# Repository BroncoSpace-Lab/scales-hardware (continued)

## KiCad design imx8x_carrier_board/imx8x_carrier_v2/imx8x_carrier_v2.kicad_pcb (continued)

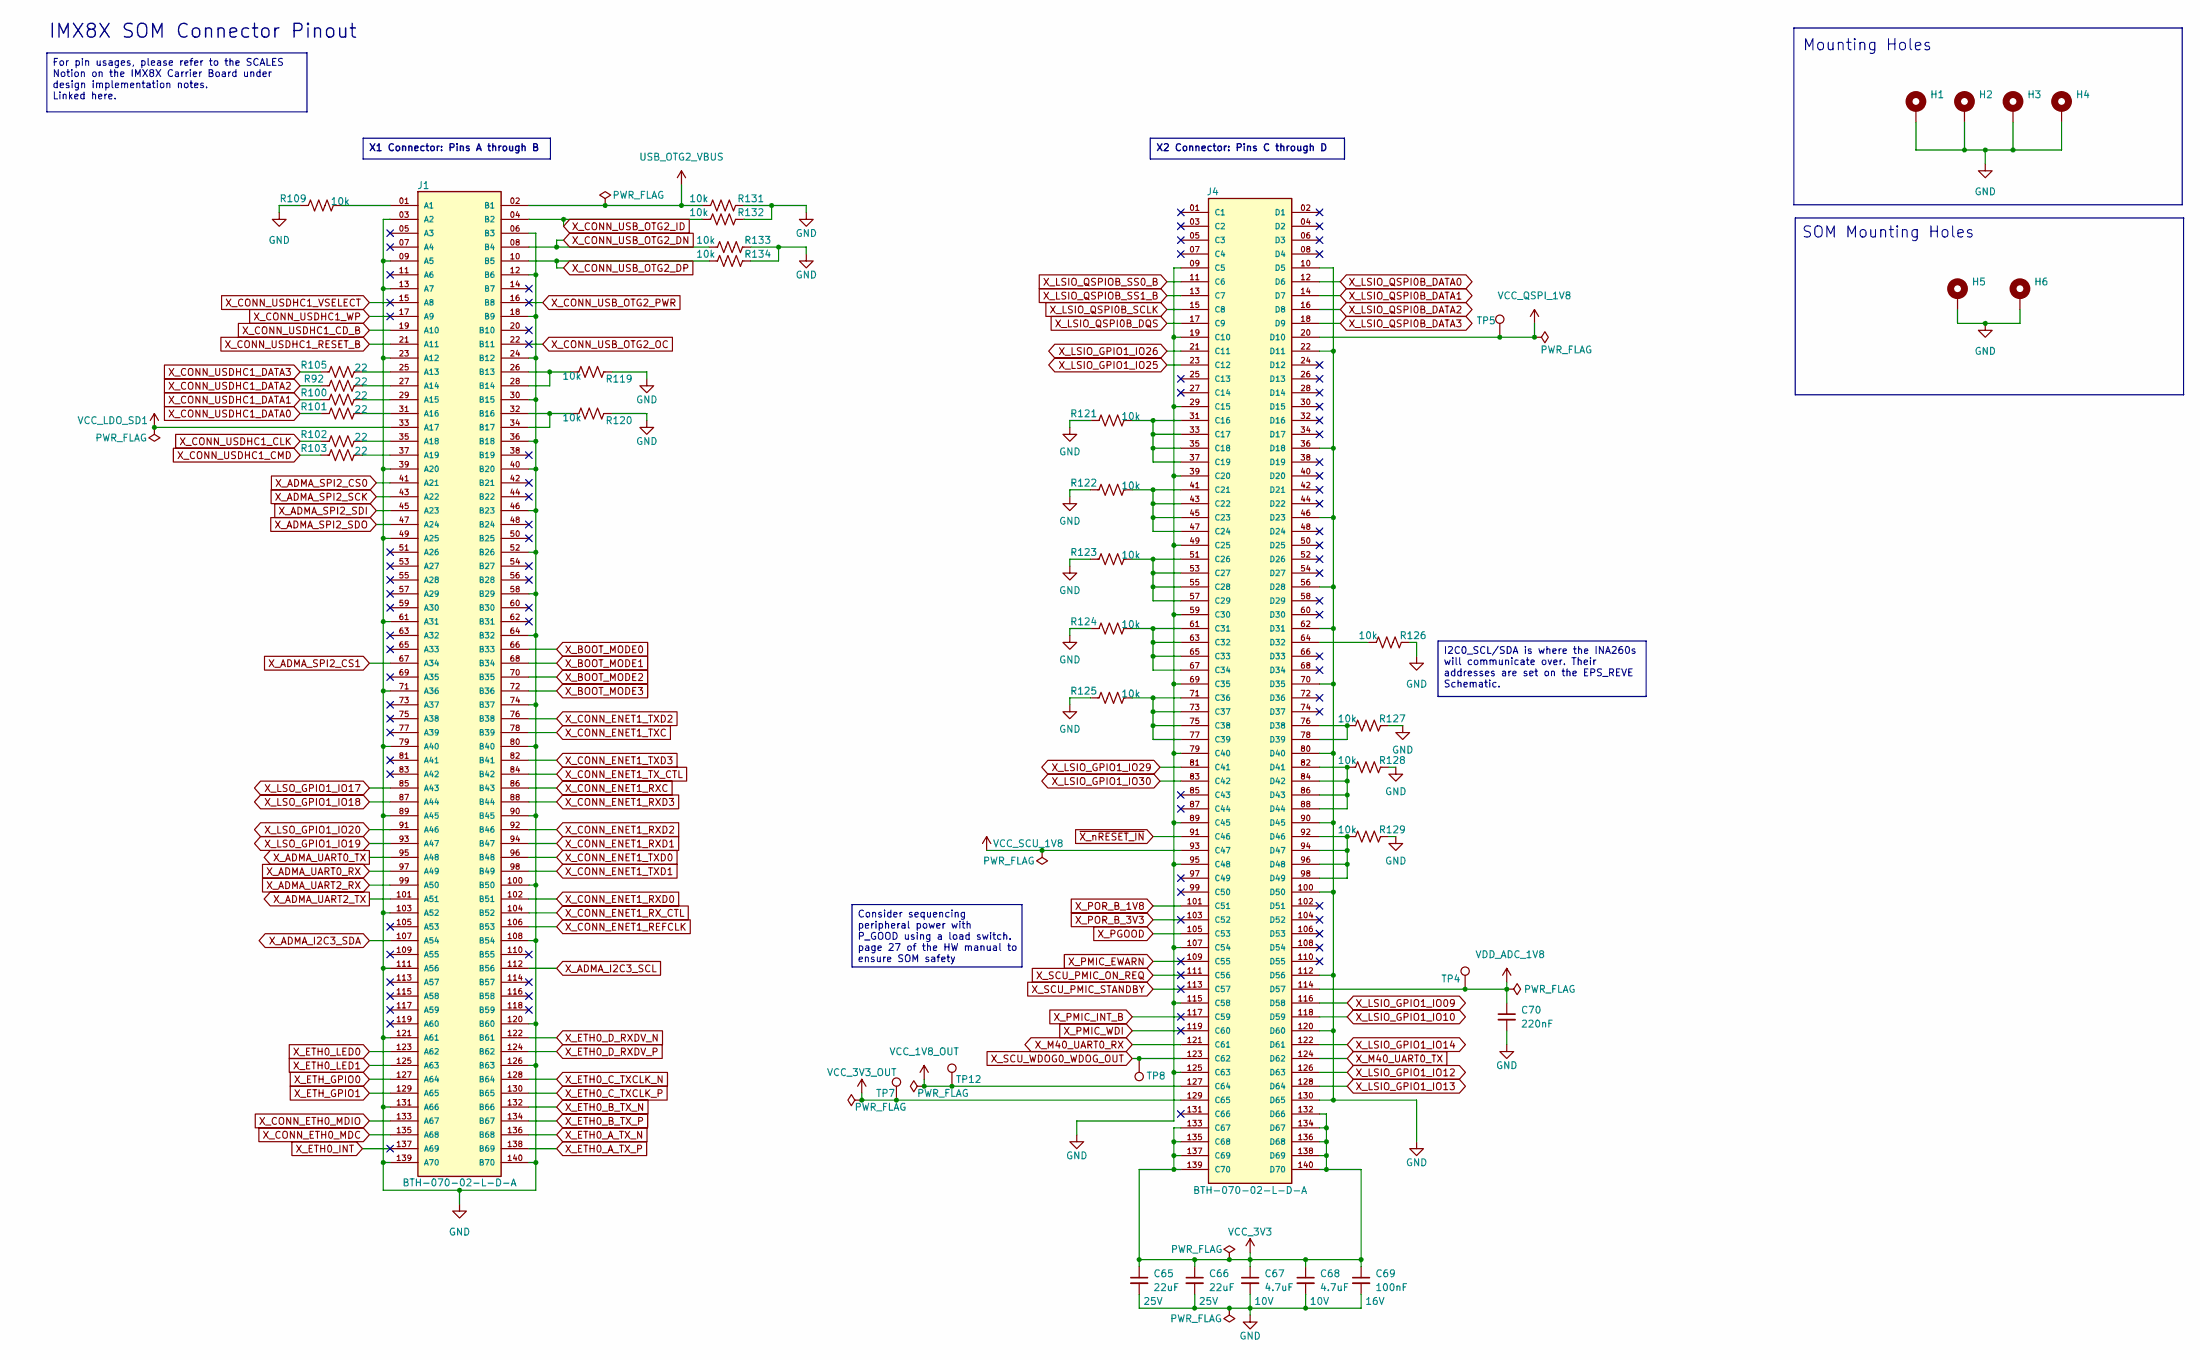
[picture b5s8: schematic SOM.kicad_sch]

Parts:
C65, C66: 22uF; C_0603_1608Metric; Voltage 25V
C67, C68: 4.7uF; C_0603_1608Metric; Voltage 10V
C69: 100nF; C_0603_1608Metric; Voltage 16V
C70: 220nF; C_0603_1608Metric
H1, H2, H3, H4: M3; MountingHole_2.7mm_M2.5_DIN965_Pad
H5, H6: MountingHole_Pad_M2.5_2.7mm; MountingHole_2.7mm_M2.5_DIN965_Pad
J1, J4: BTH-070-02-L-D-A; SAMTEC_BTH-070-02-L-D-A; PARTREV R
R92, R100, R101, R102, R103, R105: 22; R_0402_1005Metric
R109, R119, R120, R121, R122, R123, R124, R125, R126, R127, R128, R129, R131, R132, R133, R134: 10k; R_0402_1005Metric
TP4, TP5, TP7, TP8, TP12: TestPoint; TestPoint_THTPad_1.0x1.0mm_Drill0.5mm

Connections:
GND: C65.2, C66.2, C67.2, C68.2, C69.2, C70.2, H1.1 (MP), H2.1 (MP), H3.1 (MP), H4.1 (MP), H5.1 (MP), H6.1 (MP), J1.03 (A2), J1.06 (B3), J1.09 (A5), J1.12 (B6), J1.13 (A7), J1.18 (B9), J1.23 (A12), J1.24 (B12), J1.30 (B15), J1.36 (B18), J1.39 (A20), J1.40 (B20), J1.46 (B23), J1.49 (A25), J1.52 (B26), J1.58 (B29), J1.61 (A31), J1.64 (B32), J1.71 (A36), J1.74 (B37), J1.79 (A40), J1.80 (B40), J1.89 (A45), J1.90 (B45), J1.100 (B50), J1.103 (A52), J1.108 (B54), J1.111 (A56), J1.120 (B60), J1.121 (A61), J1.126 (B63), J1.131 (A66), J1.139 (A70), J1.140 (B70), J4.09 (C5), J4.10 (D5), J4.19 (C10), J4.22 (D11), J4.29 (C15), J4.36 (D18), J4.39 (C20), J4.46 (D23), J4.49 (C25), J4.56 (D28), J4.59 (C30), J4.62 (D31), J4.69 (C35), J4.70 (D35), J4.79 (C40), J4.80 (D40), J4.89 (C45), J4.90 (D45), J4.95 (C48), J4.100 (D50), J4.107 (C54), J4.112 (D56), J4.115 (C58), J4.120 (D60), J4.125 (C63), J4.130 (D65), R109.1, R119.1, R120.1, R121.1, R122.1, R123.1, R124.1, R125.1, R126.1, R127.1, R128.1, R129.1, R131.1, R132.1, R133.1, R134.1; also elsewhere on the board
unnamed: J1.01 (A1), R109.2
unnamed: J1.25 (A13), R105.2
unnamed: J1.27 (A14), R92.2
unnamed: J1.29 (A15), R100.2
unnamed: J1.31 (A16), R101.2
unnamed: J1.35 (A18), R102.2
unnamed: J1.37 (A19), R103.2
unnamed: J1.26 (B13), J1.28 (B14), R119.2
unnamed: J1.32 (B16), J1.34 (B17), R120.2
unnamed: J4.31 (C16), J4.33 (C17), J4.35 (C18), J4.37 (C19), R121.2
unnamed: J4.41 (C21), J4.43 (C22), J4.45 (C23), J4.47 (C24), R122.2
unnamed: J4.51 (C26), J4.53 (C27), J4.55 (C28), J4.57 (C29), R123.2
unnamed: J4.61 (C31), J4.63 (C32), J4.65 (C33), J4.67 (C34), R124.2
unnamed: J4.71 (C36), J4.73 (C37), J4.75 (C38), J4.77 (C39), R125.2
unnamed: J4.64 (D32), R126.2
unnamed: J4.76 (D38), J4.78 (D39), R127.2
unnamed: J4.82 (D41), J4.84 (D42), J4.86 (D43), J4.88 (D44), R128.2
unnamed: J4.92 (D46), J4.94 (D47), J4.96 (D48), J4.98 (D49), R129.2
USB_OTG2_VBUS: J1.02 (B1), R131.2
VCC_1V8_OUT: J4.127 (C64), TP12.1; also elsewhere on the board
VCC_3V3: C65.1, C66.1, C67.1, C68.1, C69.1, J4.132 (D66), J4.133 (C67), J4.134 (D67), J4.135 (C68), J4.136 (D68), J4.137 (C69), J4.138 (D69), J4.139 (C70), J4.140 (D70); also elsewhere on the board
VCC_3V3_OUT: J4.129 (C65), TP7.1; also elsewhere on the board
VCC_LDO_SD1: J1.33 (A17); also elsewhere on the board
VCC_QSPI_1V8: J4.20 (D10), TP5.1
VCC_SCU_1V8: J4.93 (C47); also elsewhere on the board
VDD_ADC_1V8: C70.1, J4.114 (D57), TP4.1
X_ADMA_I2C3_SCL: J1.112 (B56); also elsewhere on the board
X_ADMA_I2C3_SDA: J1.107 (A54); also elsewhere on the board
X_ADMA_SPI2_CS0: J1.41 (A21); also elsewhere on the board
X_ADMA_SPI2_CS1: J1.67 (A34); also elsewhere on the board
X_ADMA_SPI2_SCK: J1.43 (A22); also elsewhere on the board
X_ADMA_SPI2_SDI: J1.45 (A23); also elsewhere on the board
X_ADMA_SPI2_SDO: J1.47 (A24); also elsewhere on the board
X_ADMA_UART0_RX: J1.97 (A49); also elsewhere on the board
X_ADMA_UART0_TX: J1.95 (A48); also elsewhere on the board
X_ADMA_UART2_RX: J1.99 (A50); also elsewhere on the board
X_ADMA_UART2_TX: J1.101 (A51); also elsewhere on the board
X_BOOT_MODE0: J1.66 (B33); also elsewhere on the board
X_BOOT_MODE1: J1.68 (B34); also elsewhere on the board
X_BOOT_MODE2: J1.70 (B35); also elsewhere on the board
X_BOOT_MODE3: J1.72 (B36); also elsewhere on the board
X_CONN_ENET1_REFCLK: J1.106 (B53); also elsewhere on the board
X_CONN_ENET1_RXC: J1.86 (B43); also elsewhere on the board
X_CONN_ENET1_RXD0: J1.102 (B51); also elsewhere on the board
X_CONN_ENET1_RXD1: J1.94 (B47); also elsewhere on the board
X_CONN_ENET1_RXD2: J1.92 (B46); also elsewhere on the board
X_CONN_ENET1_RXD3: J1.88 (B44); also elsewhere on the board
X_CONN_ENET1_RX_CTL: J1.104 (B52); also elsewhere on the board
X_CONN_ENET1_TXC: J1.78 (B39); also elsewhere on the board
X_CONN_ENET1_TXD0: J1.96 (B48); also elsewhere on the board
X_CONN_ENET1_TXD1: J1.98 (B49); also elsewhere on the board
X_CONN_ENET1_TXD2: J1.76 (B38); also elsewhere on the board
X_CONN_ENET1_TXD3: J1.82 (B41); also elsewhere on the board
X_CONN_ENET1_TX_CTL: J1.84 (B42); also elsewhere on the board
X_CONN_ETH0_MDC: J1.135 (A68); also elsewhere on the board
X_CONN_ETH0_MDIO: J1.133 (A67); also elsewhere on the board
X_CONN_USB_OTG2_DN: J1.08 (B4), R133.2
X_CONN_USB_OTG2_DP: J1.10 (B5), R134.2
X_CONN_USB_OTG2_ID: J1.04 (B2), R132.2
X_CONN_USB_OTG2_OC: J1.22 (B11)
X_CONN_USB_OTG2_PWR: J1.16 (B8)
X_CONN_USDHC1_CD_B: J1.19 (A10); also elsewhere on the board
X_CONN_USDHC1_CLK: R102.1; also elsewhere on the board
X_CONN_USDHC1_CMD: R103.1; also elsewhere on the board
X_CONN_USDHC1_DATA0: R101.1; also elsewhere on the board
X_CONN_USDHC1_DATA1: R100.1; also elsewhere on the board
X_CONN_USDHC1_DATA2: R92.1; also elsewhere on the board
X_CONN_USDHC1_DATA3: R105.1; also elsewhere on the board
X_CONN_USDHC1_RESET_B: J1.21 (A11); also elsewhere on the board
X_CONN_USDHC1_VSELECT: J1.15 (A8)
X_CONN_USDHC1_WP: J1.17 (A9)
X_ETH0_A_TX_N: J1.136 (B68); also elsewhere on the board
X_ETH0_A_TX_P: J1.138 (B69); also elsewhere on the board
X_ETH0_B_TX_N: J1.132 (B66); also elsewhere on the board
X_ETH0_B_TX_P: J1.134 (B67); also elsewhere on the board
X_ETH0_C_TXCLK_N: J1.128 (B64); also elsewhere on the board
X_ETH0_C_TXCLK_P: J1.130 (B65); also elsewhere on the board
X_ETH0_D_RXDV_N: J1.122 (B61); also elsewhere on the board
X_ETH0_D_RXDV_P: J1.124 (B62); also elsewhere on the board
X_ETH0_INT: J1.137 (A69)
X_ETH0_LED0: J1.123 (A62); also elsewhere on the board
X_ETH0_LED1: J1.125 (A63); also elsewhere on the board
X_ETH_GPIO0: J1.127 (A64); also elsewhere on the board
X_ETH_GPIO1: J1.129 (A65); also elsewhere on the board
X_LSIO_GPIO1_IO09: J4.116 (D58); also elsewhere on the board
X_LSIO_GPIO1_IO10: J4.118 (D59); also elsewhere on the board
X_LSIO_GPIO1_IO12: J4.126 (D63); also elsewhere on the board
X_LSIO_GPIO1_IO13: J4.128 (D64); also elsewhere on the board
X_LSIO_GPIO1_IO14: J4.122 (D61); also elsewhere on the board
X_LSIO_GPIO1_IO25: J4.23 (C12); also elsewhere on the board
X_LSIO_GPIO1_IO26: J4.21 (C11); also elsewhere on the board
X_LSIO_GPIO1_IO29: J4.81 (C41); also elsewhere on the board
X_LSIO_GPIO1_IO30: J4.83 (C42); also elsewhere on the board
X_LSIO_QSPI0B_DATA0: J4.12 (D6); also elsewhere on the board
X_LSIO_QSPI0B_DATA1: J4.14 (D7); also elsewhere on the board
X_LSIO_QSPI0B_DATA2: J4.16 (D8); also elsewhere on the board
X_LSIO_QSPI0B_DATA3: J4.18 (D9); also elsewhere on the board
X_LSIO_QSPI0B_DQS: J4.17 (C9); also elsewhere on the board
X_LSIO_QSPI0B_SCLK: J4.15 (C8); also elsewhere on the board
X_LSIO_QSPIOB_SS0_B: J4.11 (C6); also elsewhere on the board
X_LSIO_QSPIOB_SS1_B: J4.13 (C7); also elsewhere on the board
X_LSO_GPIO1_IO17: J1.85 (A43); also elsewhere on the board
X_LSO_GPIO1_IO18: J1.87 (A44); also elsewhere on the board
X_LSO_GPIO1_IO19: J1.93 (A47); also elsewhere on the board
X_LSO_GPIO1_IO20: J1.91 (A46); also elsewhere on the board
X_M40_UART0_RX: J4.121 (C61); also elsewhere on the board
X_M40_UART0_TX: J4.124 (D62); also elsewhere on the board
X_PGOOD: J4.105 (C53); also elsewhere on the board
X_PMIC_EWARN: J4.109 (C55)
X_PMIC_INT_B: J4.117 (C59)
X_PMIC_WDI: J4.119 (C60)
X_POR_B_1V8: J4.101 (C51); also elsewhere on the board
X_POR_B_3V3: J4.103 (C52)
X_SCU_PMIC_ON_REQ: J4.111 (C56)
X_SCU_PMIC_STANDBY: J4.113 (C57)
X_SCU_WDOG0_WDOG_OUT: J4.123 (C62), TP8.1; also elsewhere on the board
~X_nRESET_IN: J4.91 (C46); also elsewhere on the board

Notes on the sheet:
Mounting Holes
SOM Mounting Holes
IMX8X SOM Connector Pinout
Consider sequencing peripheral power with P_GOOD using a load switch. page 27 of the HW manual to ensure SOM safety
X2 Connector: Pins C through D
I2C0_SCL/SDA is where the INA260s will communicate over. Their addresses are set on the EPS_REVE Schematic.
For pin usages, please refer to the SCALES Notion on the IMX8X Carrier Board under design implementation notes. Linked here.
X1 Connector: Pins A through B

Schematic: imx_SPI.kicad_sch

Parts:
J6: Conn_02x07_Counter_Clockwise; PinHeader_2x07_P2.54mm_Vertical

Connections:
GND: J6.8; also elsewhere on the board
X_ADMA_SPI2_CS0: J6.1; also elsewhere on the board
X_ADMA_SPI2_CS1: J6.2; also elsewhere on the board
X_ADMA_SPI2_SCK: J6.3; also elsewhere on the board
X_ADMA_SPI2_SDI: J6.4; also elsewhere on the board
X_ADMA_SPI2_SDO: J6.5; also elsewhere on the board
X_LSIO_QSPI0B_DATA0: J6.11; also elsewhere on the board
X_LSIO_QSPI0B_DATA1: J6.12; also elsewhere on the board
X_LSIO_QSPI0B_DATA2: J6.13; also elsewhere on the board
X_LSIO_QSPI0B_DATA3: J6.14; also elsewhere on the board
X_LSIO_QSPI0B_DQS: J6.10; also elsewhere on the board
X_LSIO_QSPI0B_SCLK: J6.9; also elsewhere on the board
X_LSIO_QSPIOB_SS0_B: J6.6; also elsewhere on the board
X_LSIO_QSPIOB_SS1_B: J6.7; also elsewhere on the board

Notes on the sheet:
QSPI-SPI

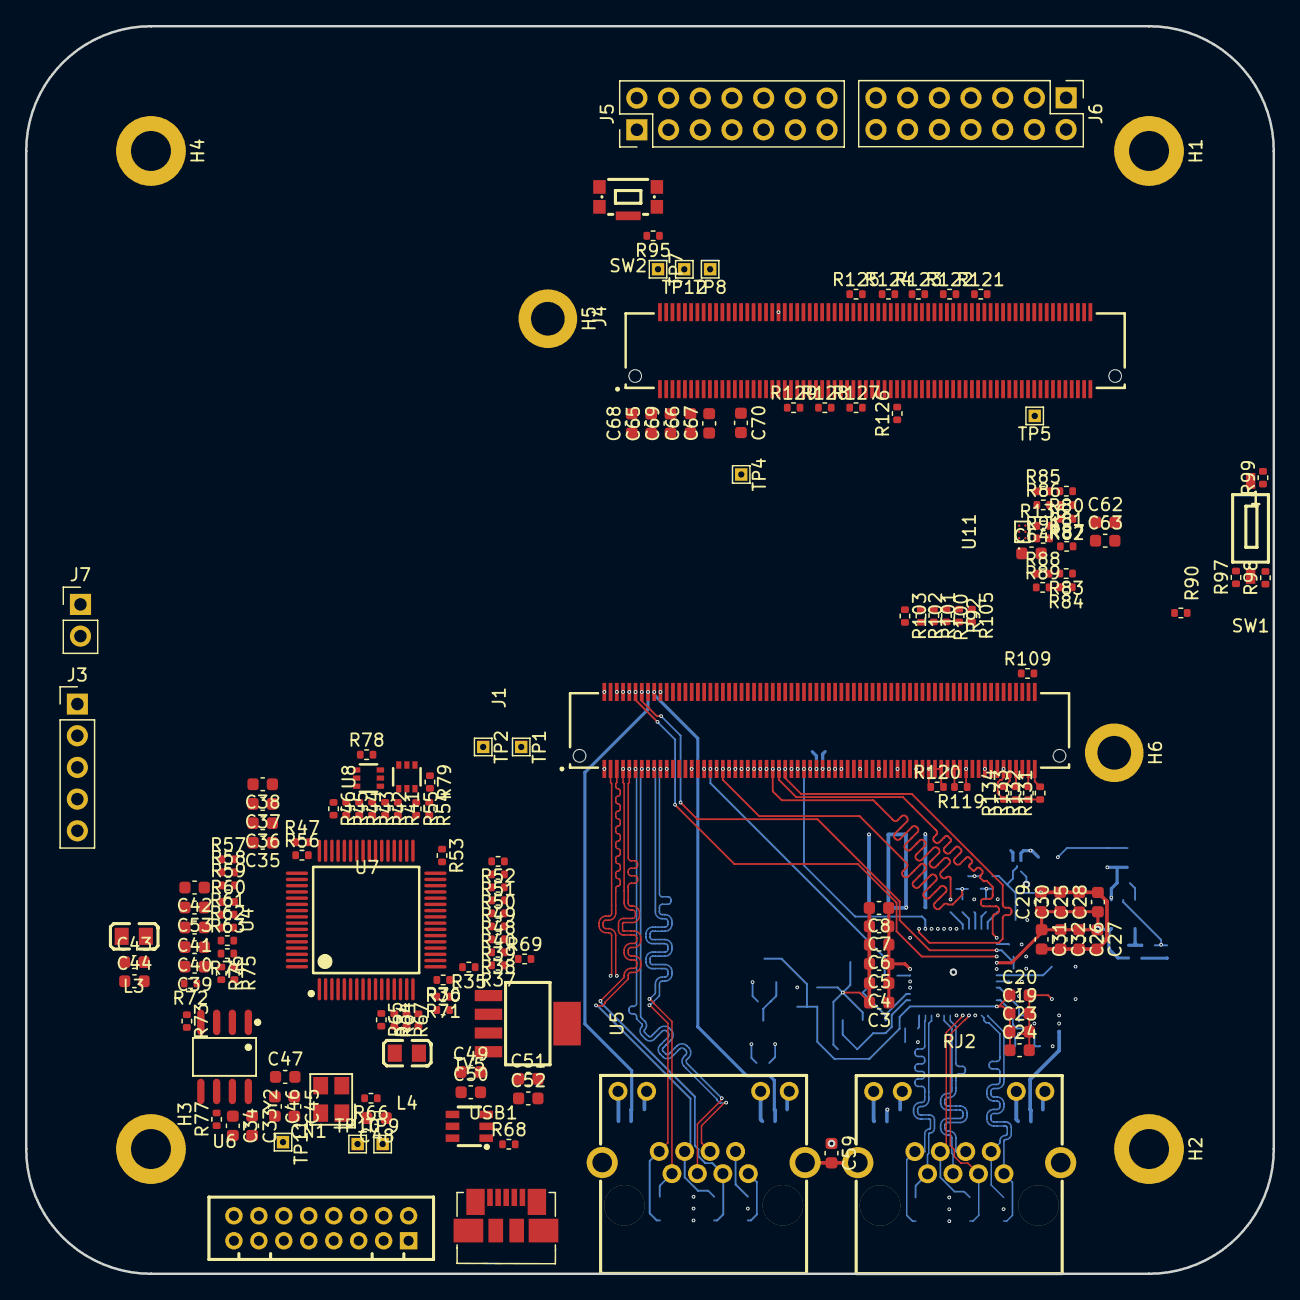
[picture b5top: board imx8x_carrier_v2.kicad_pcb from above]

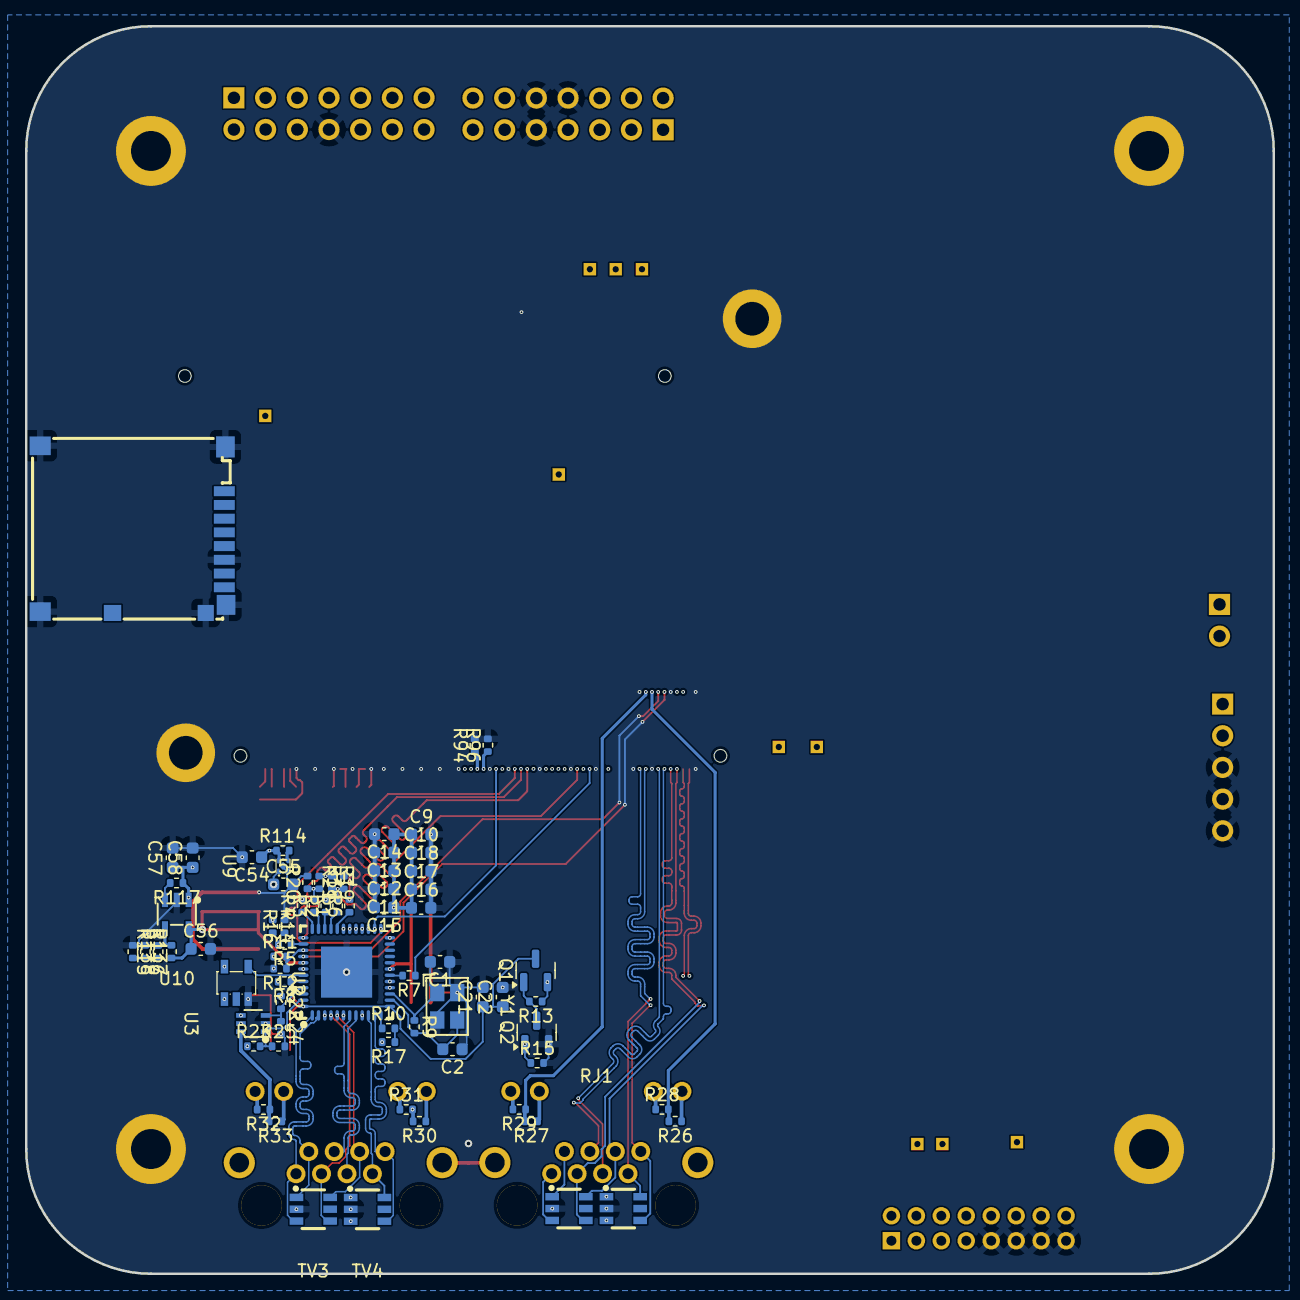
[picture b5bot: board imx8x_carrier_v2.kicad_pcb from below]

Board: 6 copper layers, 100.0 x 100.0 mm, 245 parts (73 on the bottom side), 215 nets.

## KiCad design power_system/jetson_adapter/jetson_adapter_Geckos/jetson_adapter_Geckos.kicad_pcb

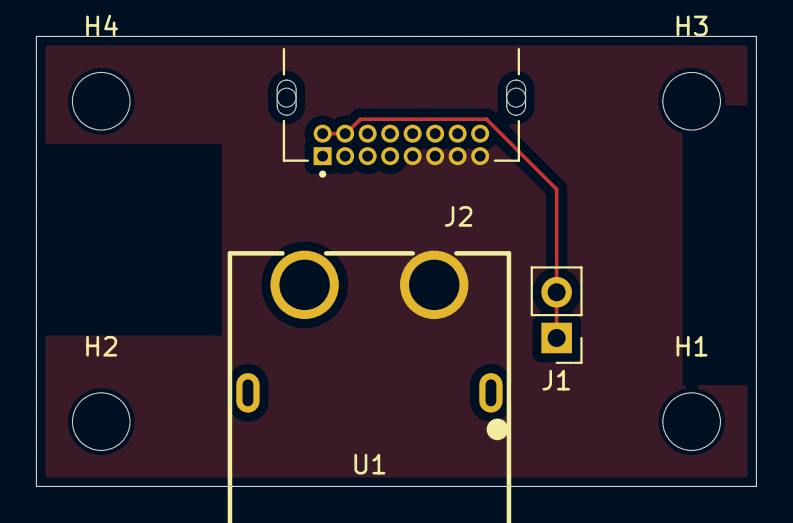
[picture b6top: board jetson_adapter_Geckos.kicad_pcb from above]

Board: 2 copper layers, 40.0 x 25.0 mm, 7 parts (0 on the bottom side), 3 nets.

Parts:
H1, H2, H3, H4: MountingHole; MountingHole_3.2mm_M3
J1: Conn_01x02_Pin; PinHeader_1x02_P2.54mm_Vertical
J2: G125-MH11605L1P; HARWIN_G125-MH11605L1P
U1: XT60PW-F_C428722; TH_2P-XT60PW-F

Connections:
+20V_J: J2.5, J2.6, J2.7, J2.8, U1.3 (+)
GND: J2.1, J2.2, J2.3, J2.4, U1.1, U1.2, U1.4 (-)
WDT_WDI_Jetson: J1.1, J1.2, J2.9, J2.10

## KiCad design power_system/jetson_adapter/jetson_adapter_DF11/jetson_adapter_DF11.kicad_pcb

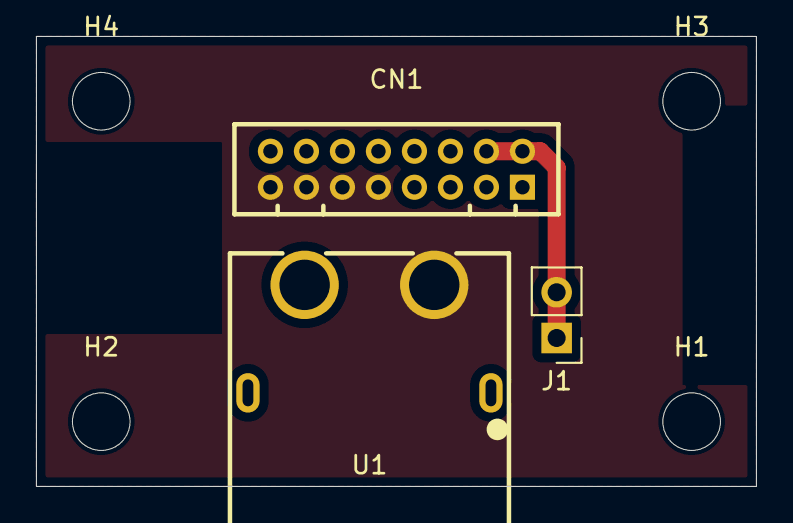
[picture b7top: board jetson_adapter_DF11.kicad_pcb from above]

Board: 2 copper layers, 40.0 x 25.0 mm, 7 parts (0 on the bottom side), 3 nets.

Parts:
CN1: DF11-16DP-2DSA(08); CONN-TH_DF11-16DP-2DSA-08
H1, H2, H3, H4: MountingHole; MountingHole_3.2mm_M3
J1: Conn_01x02_Pin; PinHeader_1x02_P2.54mm_Vertical
U1: XT60PW-F_C428722; TH_2P-XT60PW-F

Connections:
+20V_J: CN1.9, CN1.11, CN1.13, CN1.15, U1.3 (+)
GND: CN1.1, CN1.3, CN1.5, CN1.7, U1.1, U1.2, U1.4 (-)
WDT_WDI_Jetson: CN1.2, CN1.4, J1.1, J1.2
